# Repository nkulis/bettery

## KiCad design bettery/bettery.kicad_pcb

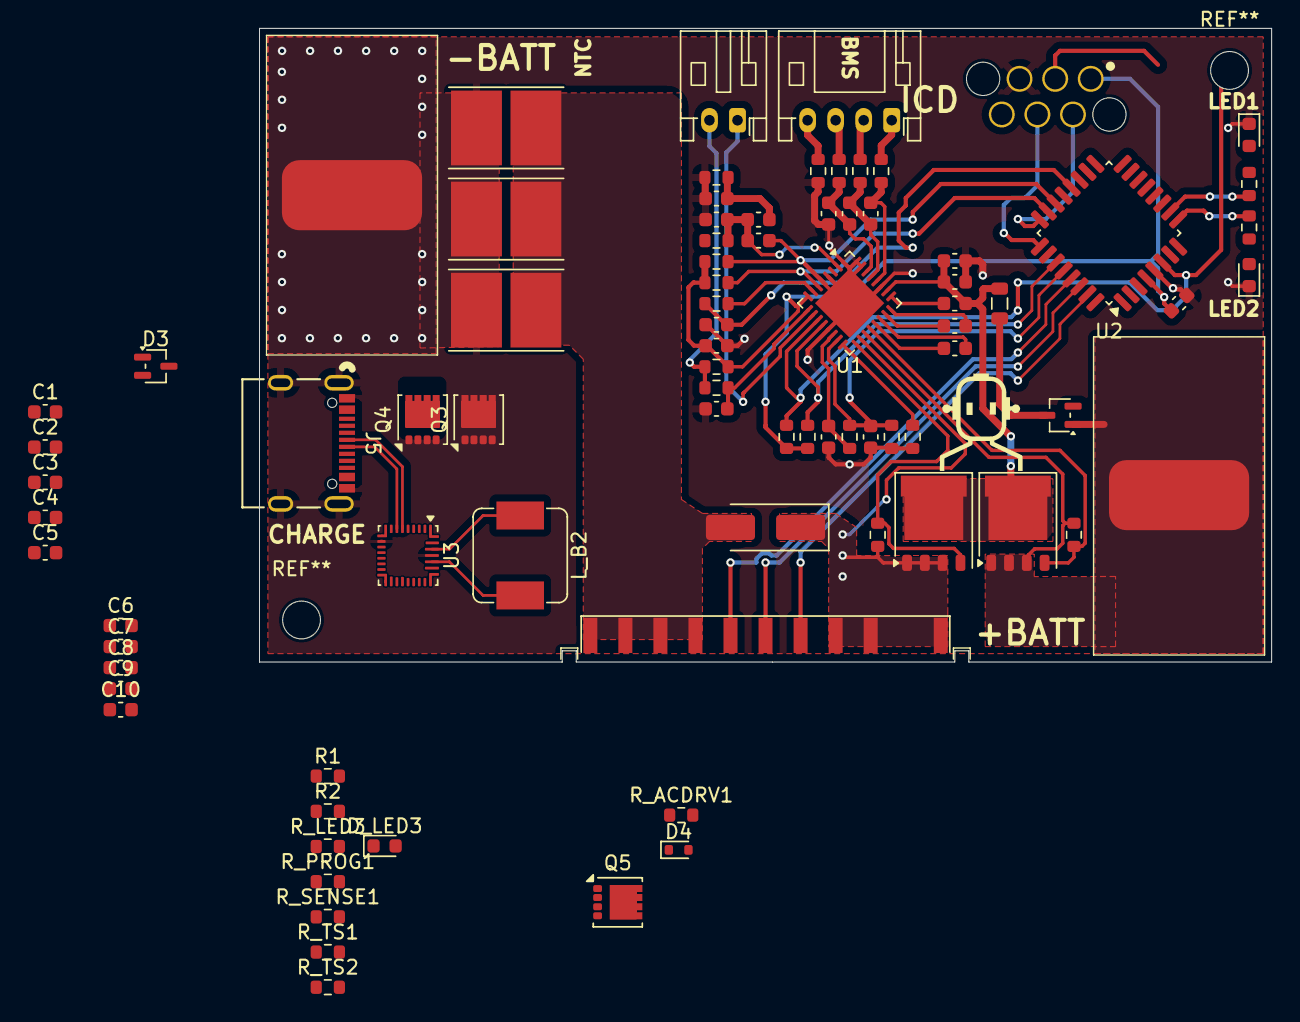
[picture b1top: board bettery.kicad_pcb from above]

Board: 2 copper layers, 72.2 x 45.2 mm, 83 parts (0 on the bottom side), 65 nets.

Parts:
C1, C2: 4.7n; C_0603_1608Metric
C3: 4.7u; C_0603_1608Metric
C4, C5, C6, C7, C8, C9, C10: 10u; C_0603_1608Metric
C_B1, C_B3: 10u; C_0603_1608Metric
C_B2: 220n; C_0603_1608Metric
C_CP1: 68n; C_0603_1608Metric
C_CP_1, C_CP_2: 6.8n; C_0603_1608Metric
C_FILL1: 10n; C_0603_1608Metric
C_ISENSE_1: 4.7u; C_0603_1608Metric
C_ISENSE_2: 22n; C_0603_1608Metric
C_ISENSE_CM1, C_ISENSE_CM2: 4.7u; C_0603_1608Metric
C_LPF1, C_LPF2, C_LPF3: 470n; C_0603_1608Metric
C_NSHIP1: 100n; C_0603_1608Metric
C_RDY1: 100p; C_0603_1608Metric
C_VREG1: 4.7u; C_0603_1608Metric
C_WAKEUP1: 100n; C_0603_1608Metric
D1, D3: BAT54SWFILMY; SOT-323_SC-70
D2: SS54; D_SMA_Handsoldering
D4: BZT52C12T-7; D_SOD-523
D_LED1, D_LED2, D_LED3: LED; LED_0603_1608Metric
H1, H2: MountingHole_Pad; SolderWirePad_1x01_SMD_5x10mm
J1: JST_PH_S4B-PH-K_1x04_P2.00mm_Horizontal
J2: Conn_01x10_Socket; 1674231_SMD
J3: JST_PH_S2B-PH-K_1x02_P2.00mm_Horizontal
J4: Conn_ARM_SWD_TagConnect_TC2030; WR-WST-REDFIT-IDC-6pin
J5: CONN12_RAHUC31_SWC
L_B1: 1u; L_0805_2012Metric
L_B2: 1u; L_Sumida_CDMC6D28_7.25x6.5mm
Q1, Q2: WMB014N06LG4; WMB014N06LG4-PDFN5060-8L
Q3: CSD17575Q3; VSON-8_3.3x3.3mm_P0.65mm_NexFET
Q4, Q5: CSD17581Q3A; VSON-8_3.3x3.3mm_P0.65mm_NexFET
R1, R2: 10.5k; R_0603_1608Metric
R_ACDRV1: 294; R_0603_1608Metric
R_CHG1: 2M; R_0603_1608Metric
R_DCHG1: 2M; R_0603_1608Metric
R_FIL1: 10k; R_0603_1608Metric
R_FLTS_UP1: 4.7k; R_0603_1608Metric
R_FLT_UP1: 4.7k; R_0603_1608Metric
R_FUSE1: 10k; R_0603_1608Metric
R_ISENSE1, R_ISENSE2: 22; R_0603_1608Metric
R_LED1, R_LED2, R_LED3: 2.2k; R_0603_1608Metric
R_LPF1, R_LPF2, R_LPF3, R_LPF4: 39; R_0603_1608Metric
R_NSHIP_PD1: 100k; R_0603_1608Metric
R_PROG1: 10.5k; R_0603_1608Metric
R_PU1: 33k; R_0603_1608Metric
R_RDY1: 100; R_0603_1608Metric
R_SCL_UP1: 4.7k; R_0603_1608Metric
R_SDA_UP1: 4.7k; R_0603_1608Metric
R_SENSE1: 100; R_0603_1608Metric
R_SHUNT1, R_SHUNT2, R_SHUNT3: 6m; R_Shunt_Vishay_WSHP2818
R_TS1, R_TS2: 10.5k; R_0603_1608Metric
R_WAKEUP1: 1k; R_0603_1608Metric
U1: L9961; UFQFPN-32-1EP_5x5mm_P0.5mm_EP3.5x3.5mm
U2: STM32G070KBTx; LQFP-32_7x7mm_P0.8mm
U3: BQ25798; Texas_RQM0029A_VQFN-29_4x4mm_P0.4mm

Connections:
+3.3V: C_VREG1.1, R_FLTS_UP1.1, R_FLT_UP1.2, R_PU1.1, R_SCL_UP1.2, R_SDA_UP1.2, U1.8 (VREG), U2.4 (VDD)
+BATT: D1.1 (A), H1.1, Q1.1 (S), R_CHG1.1, U1.19 (VSC)
+PACK: D2.1 (K), J2.1, J2.2, J2.3, Q2.1 (S), Q3.1 (S), Q3.2 (S), Q3.3 (S), R_DCHG1.1, R_SENSE1.2, U1.18 (VSD)
-BATT: C3.2, C4.2, C5.2, C6.2, C7.2, C8.2, C9.2, C10.2, C_B1.2, C_B2.2, C_B3.2, C_FILL1.2, C_ISENSE_CM1.1, C_ISENSE_CM2.2, C_LPF1.2, C_NSHIP1.2, C_RDY1.2, C_VREG1.2, C_WAKEUP1.2, D_LED1.1 (K), D_LED2.1 (K), H2.1, J4.5 (GND), J5.A1 (GND), J5.B1 (GND), J5.S1 (SHIELD), R2.2, R_FUSE1.2, R_ISENSE1.2, R_LPF1.2, R_NSHIP_PD1.1, R_PROG1.2, R_SHUNT1.1, R_SHUNT2.1, R_SHUNT3.1, R_TS2.1, U1.1 (C0), U1.4 (GND), U1.13 (GND), U1.27 (GND), U1.31 (C2), U1.32 (C1), U2.5 (VSS), U3.10 (ACDRV2), U3.27 (GND)
-PACK: D2.2 (A), J2.7, J2.8, J2.9, J2.10, R_ISENSE2.2, R_SHUNT1.2, R_SHUNT2.2, R_SHUNT3.2
/C3: C_LPF1.1, C_LPF2.2, R_LPF2.2, U1.30 (C3)
/C4: C_LPF2.1, C_LPF3.2, R_LPF3.2, U1.29 (C4)
/C5: C_LPF3.1, R_LPF4.2, U1.28 (C5)
/CHG: Q1.2 (G), R_CHG1.2, U1.20 (CHG)
/DCHG: Q2.2 (G), R_DCHG1.2, U1.17 (DCHG)
/FAULTN: R_FLT_UP1.1, U1.12 (FAULTN), U2.27 (PB3)
/FAULTN_SAFE: R_FLTS_UP1.2, U1.11 (FAULTN_SAFE), U2.6 (NRST)
/HOST_SCL: J2.5, U2.30 (I2C1_SCL)
/HOST_SDA: J2.4, U2.31 (I2C1_SDA)
/HOST_SMBA: J2.6, U2.29 (I2C1_SMBA)
/I2C2_SCL: U1.5 (SCL), U2.22 (I2C2_SCL (PA11)), U3.14 (SCL)
/I2C2_SDA: U1.6 (SDA), U2.23 (I2C2_SDA (PA12)), U3.15 (SDA)
/ISENSEM: C_ISENSE_1.1, C_ISENSE_1.2, C_ISENSE_2.1, C_ISENSE_2.2, C_ISENSE_CM1.2, C_ISENSE_CM2.1, R_ISENSE1.1, R_ISENSE2.1, U1.2 (ISENSEP), U1.3 (ISENSEM)
/LED1: R_LED1.1, U2.10 (TIM15_CH2)
/LED2: R_LED2.1, U2.9 (TIM15_CH1)
/NSHIP: C_NSHIP1.1, R_NSHIP_PD1.2, R_WAKEUP1.2, U1.15 (NSHIP), U2.28 (PB4)
/NTC: C_FILL1.1, R_FIL1.1, U1.9 (NTC)
/OD: J3.1, U1.10 (OD)
/RDY: C_RDY1.1, R_RDY1.1, U2.20 (PC6)
/REGN: C3.1, R1.1, R_LED3.2, R_TS1.2, U3.5 (REGN)
/SWCLK: J4.4 (SWCLK), U2.25 (SYS_SWCLK)
/SWDIO: J4.2 (SWDIO), U2.24 (SYS_SWDIO)
/TS: R_TS1.1, R_TS2.2, U3.16 (TS)
/VB: C_B1.1, C_B2.1, C_CP1.2, L_B1.2, Q1.3 (D), Q2.3 (D), U1.26 (VB)
/VREG: C_B3.1, J4.1 (VCC)
/WAKEUP: C_WAKEUP1.1, R_WAKEUP1.1, U1.14 (WAKEUP)
unnamed: D1.3 (K), L_B1.1
unnamed: D4.2 (A), Q4.1 (S), Q4.2 (S), Q4.3 (S), Q5.1 (S), Q5.2 (S), Q5.3 (S)
unnamed: D4.1 (K), Q4.4 (G), Q5.4 (G), R_ACDRV1.2
unnamed: D_LED1.2 (A), R_LED1.2
unnamed: D_LED2.2 (A), R_LED2.2
unnamed: D_LED3.2 (A), R_LED3.1
unnamed: D_LED3.1 (K), U3.1 (STAT)
unnamed: J1.1, R_LPF4.1
unnamed: J1.2, R_LPF3.1
unnamed: J1.3, R_LPF2.1
unnamed: J1.4, R_LPF1.1
unnamed: J3.2, R_FIL1.2, R_PU1.2
unnamed: C9.1, C10.1, Q3.5 (D), U3.22 (BAT), U3.23 (BAT)
unnamed: Q3.4 (G), U3.24 (SDRV)
unnamed: J5.A4 (VBUS), J5.B4 (VBUS), Q4.5 (D), U3.9 (VAC1)
unnamed: Q5.5 (D), U3.2 (VBUS), U3.3 (VBUS), U3.8 (VAC2)
unnamed: R_FUSE1.1, U1.16 (FUSE)
unnamed: R_RDY1.2, U1.7 (RDY)
unnamed: C_CP_1.2, U1.21 (VCP1M)
unnamed: C_CP_1.1, U1.22 (VCP1P)
unnamed: C_CP_2.2, U1.23 (VCP2M)
unnamed: C_CP_2.1, U1.24 (VCP2P)
unnamed: C_CP1.1, U1.25 (VCP)
unnamed: R_ACDRV1.1, U3.11 (ACDRV1)
unnamed: R_SENSE1.1, U3.18 (BATP)
unnamed: C2.1, U3.4 (BTST1)
unnamed: C1.2, U3.19 (BTST2)
unnamed: J5.A6 (D+), J5.B6 (D+), U3.6 (D+)
unnamed: J5.A7 (D-), J5.B7 (D-), U3.7 (D-)
unnamed: R1.2, R2.1, U3.17 (ILIM_HIZ)
unnamed: R_PROG1.1, U3.20 (PROG)
unnamed: C2.2, L_B2.1, U3.28 (SW1)
unnamed: C1.1, L_B2.2, U3.26 (SW2)
unnamed: C4.1, C5.1, C6.1, C7.1, C8.1, U3.25 (SYS)

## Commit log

2026-01-13 remove fail-safe switch
2026-01-14 add mcu
2026-01-16 complete routing
2026-01-17 sync
2026-01-17 move ntc connector to top side of the board
2026-04-03 add chassis models
